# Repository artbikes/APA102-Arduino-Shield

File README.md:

# APA102-Arduino-Shield
An APA102 Arduino shield influenced by the Neopixel shield offered by Adafruit.
http://imgur.com/a/hvsxp

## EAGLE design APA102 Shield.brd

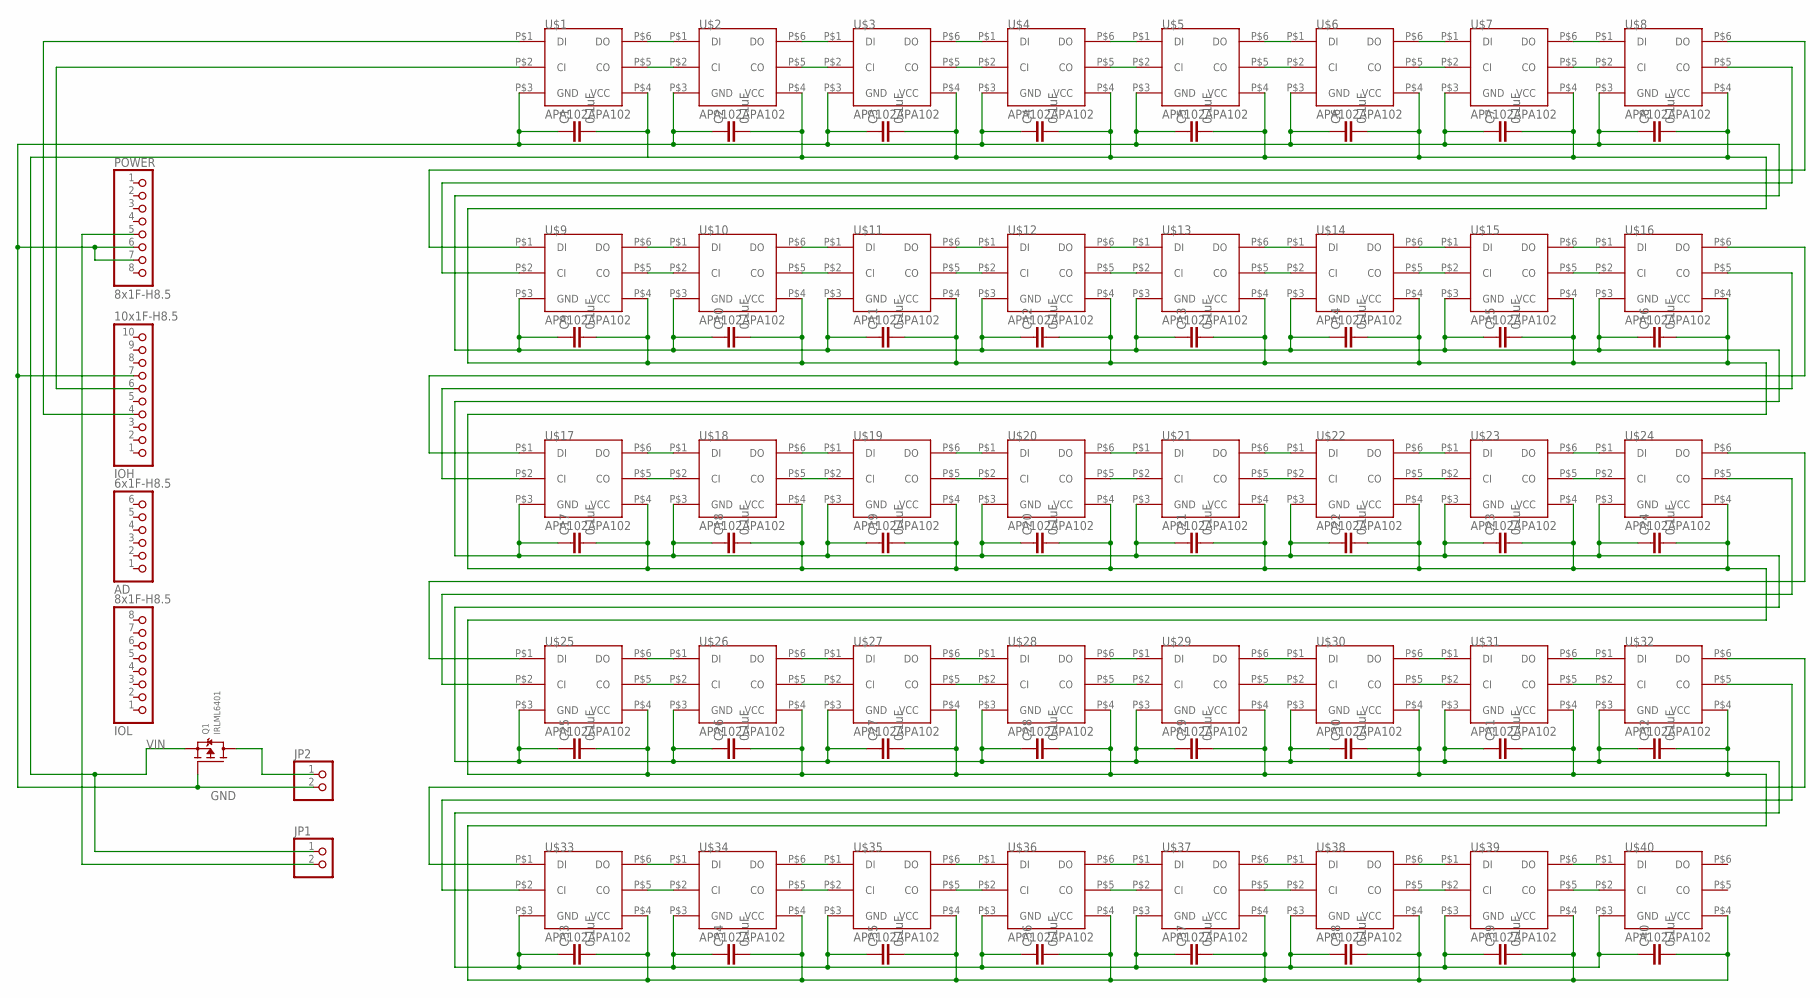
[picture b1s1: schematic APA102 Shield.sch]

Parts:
AD: 6x1F-H8.5; 1X06
C1, C2, C3, C4, C5, C6, C7, C8, C9, C10, C11, C12, C13, C14, C15, C16, C17, C18, C19, C20, C21, C22, C23, C24, C25, C26, C27, C28, C29, C30, C31, C32, C33, C34, C35, C36, C37, C38, C39, C40: 0.1uF; C1206
IOH: 10x1F-H8.5; 1X10
IOL: 8x1F-H8.5; 1X08
JP1, JP2: PINHD-1X2; 1X02
POWER: 8x1F-H8.5; 1X08
Q1: IRLML6401; SOT23-WIDE
U$1, U$2, U$3, U$4, U$5, U$6, U$7, U$8, U$9, U$10, U$11, U$12, U$13, U$14, U$15, U$16, U$17, U$18, U$19, U$20, U$21, U$22, U$23, U$24, U$25, U$26, U$27, U$28, U$29, U$30, U$31, U$32, U$33, U$34, U$35, U$36, U$37, U$38, U$39, U$40: APA102APA102; 5050

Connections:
GND: C1.1, C2.1, C3.1, C4.1, C5.1, C6.1, C7.1, C8.1, C9.1, C10.1, C11.1, C12.1, C13.1, C14.1, C15.1, C16.1, C17.1, C18.1, C19.1, C20.1, C21.1, C22.1, C23.1, C24.1, C25.1, C26.1, C27.1, C28.1, C29.1, C30.1, C31.1, C32.1, C33.1, C34.1, C35.1, C36.1, C37.1, C38.1, C39.1, C40.1, IOH.7, JP2.2, POWER.6, POWER.7, Q1.1 (G), U$1.P$3 (GND), U$2.P$3 (GND), U$3.P$3 (GND), U$4.P$3 (GND), U$5.P$3 (GND), U$6.P$3 (GND), U$7.P$3 (GND), U$8.P$3 (GND), U$9.P$3 (GND), U$10.P$3 (GND), U$11.P$3 (GND), U$12.P$3 (GND), U$13.P$3 (GND), U$14.P$3 (GND), U$15.P$3 (GND), U$16.P$3 (GND), U$17.P$3 (GND), U$18.P$3 (GND), U$19.P$3 (GND), U$20.P$3 (GND), U$21.P$3 (GND), U$22.P$3 (GND), U$23.P$3 (GND), U$24.P$3 (GND), U$25.P$3 (GND), U$26.P$3 (GND), U$27.P$3 (GND), U$28.P$3 (GND), U$29.P$3 (GND), U$30.P$3 (GND), U$31.P$3 (GND), U$32.P$3 (GND), U$33.P$3 (GND), U$34.P$3 (GND), U$35.P$3 (GND), U$36.P$3 (GND), U$37.P$3 (GND), U$38.P$3 (GND), U$39.P$3 (GND), U$40.P$3 (GND)
unnamed: IOH.4, U$1.P$1 (DI)
unnamed: U$15.P$5 (CO), U$16.P$2 (CI)
unnamed: U$23.P$6 (DO), U$24.P$1 (DI)
unnamed: U$15.P$6 (DO), U$16.P$1 (DI)
unnamed: IOH.6, U$1.P$2 (CI)
unnamed: U$14.P$6 (DO), U$15.P$1 (DI)
unnamed: U$14.P$5 (CO), U$15.P$2 (CI)
unnamed: U$7.P$6 (DO), U$8.P$1 (DI)
unnamed: U$7.P$5 (CO), U$8.P$2 (CI)
unnamed: U$6.P$6 (DO), U$7.P$1 (DI)
unnamed: U$6.P$5 (CO), U$7.P$2 (CI)
unnamed: U$5.P$6 (DO), U$6.P$1 (DI)
unnamed: U$5.P$5 (CO), U$6.P$2 (CI)
unnamed: U$4.P$6 (DO), U$5.P$1 (DI)
unnamed: U$4.P$5 (CO), U$5.P$2 (CI)
unnamed: U$3.P$6 (DO), U$4.P$1 (DI)
unnamed: U$3.P$5 (CO), U$4.P$2 (CI)
unnamed: U$2.P$6 (DO), U$3.P$1 (DI)
unnamed: U$2.P$5 (CO), U$3.P$2 (CI)
unnamed: U$1.P$6 (DO), U$2.P$1 (DI)
unnamed: U$1.P$5 (CO), U$2.P$2 (CI)
unnamed: U$23.P$5 (CO), U$24.P$2 (CI)
unnamed: U$13.P$6 (DO), U$14.P$1 (DI)
unnamed: U$22.P$6 (DO), U$23.P$1 (DI)
unnamed: U$13.P$5 (CO), U$14.P$2 (CI)
unnamed: U$12.P$6 (DO), U$13.P$1 (DI)
unnamed: U$12.P$5 (CO), U$13.P$2 (CI)
unnamed: U$11.P$6 (DO), U$12.P$1 (DI)
unnamed: U$11.P$5 (CO), U$12.P$2 (CI)
unnamed: U$10.P$6 (DO), U$11.P$1 (DI)
unnamed: U$10.P$5 (CO), U$11.P$2 (CI)
unnamed: U$9.P$6 (DO), U$10.P$1 (DI)
unnamed: U$9.P$5 (CO), U$10.P$2 (CI)
unnamed: U$22.P$5 (CO), U$23.P$2 (CI)
unnamed: U$16.P$5 (CO), U$17.P$2 (CI)
unnamed: U$8.P$5 (CO), U$9.P$2 (CI)
unnamed: U$8.P$6 (DO), U$9.P$1 (DI)
unnamed: U$16.P$6 (DO), U$17.P$1 (DI)
unnamed: U$39.P$6 (DO), U$40.P$1 (DI)
unnamed: U$21.P$6 (DO), U$22.P$1 (DI)
unnamed: U$21.P$5 (CO), U$22.P$2 (CI)
unnamed: U$20.P$6 (DO), U$21.P$1 (DI)
unnamed: U$20.P$5 (CO), U$21.P$2 (CI)
unnamed: U$19.P$6 (DO), U$20.P$1 (DI)
unnamed: U$19.P$5 (CO), U$20.P$2 (CI)
unnamed: U$18.P$6 (DO), U$19.P$1 (DI)
unnamed: U$18.P$5 (CO), U$19.P$2 (CI)
unnamed: U$17.P$6 (DO), U$18.P$1 (DI)
unnamed: U$17.P$5 (CO), U$18.P$2 (CI)
unnamed: U$39.P$5 (CO), U$40.P$2 (CI)
unnamed: U$38.P$6 (DO), U$39.P$1 (DI)
unnamed: U$31.P$6 (DO), U$32.P$1 (DI)
unnamed: U$31.P$5 (CO), U$32.P$2 (CI)
unnamed: U$30.P$6 (DO), U$31.P$1 (DI)
unnamed: U$30.P$5 (CO), U$31.P$2 (CI)
unnamed: U$29.P$6 (DO), U$30.P$1 (DI)
unnamed: U$29.P$5 (CO), U$30.P$2 (CI)
unnamed: U$28.P$6 (DO), U$29.P$1 (DI)
unnamed: U$28.P$5 (CO), U$29.P$2 (CI)
unnamed: U$27.P$6 (DO), U$28.P$1 (DI)
unnamed: U$27.P$5 (CO), U$28.P$2 (CI)
unnamed: U$26.P$6 (DO), U$27.P$1 (DI)
unnamed: U$26.P$5 (CO), U$27.P$2 (CI)
unnamed: U$25.P$6 (DO), U$26.P$1 (DI)
unnamed: U$25.P$5 (CO), U$26.P$2 (CI)
unnamed: U$38.P$5 (CO), U$39.P$2 (CI)
unnamed: U$24.P$5 (CO), U$25.P$2 (CI)
unnamed: U$24.P$6 (DO), U$25.P$1 (DI)
unnamed: JP1.2, POWER.5
unnamed: JP2.1, Q1.3 (D)
unnamed: U$37.P$6 (DO), U$38.P$1 (DI)
unnamed: U$37.P$5 (CO), U$38.P$2 (CI)
unnamed: U$36.P$6 (DO), U$37.P$1 (DI)
unnamed: U$36.P$5 (CO), U$37.P$2 (CI)
unnamed: U$35.P$6 (DO), U$36.P$1 (DI)
unnamed: U$35.P$5 (CO), U$36.P$2 (CI)
unnamed: U$34.P$6 (DO), U$35.P$1 (DI)
unnamed: U$34.P$5 (CO), U$35.P$2 (CI)
unnamed: U$33.P$6 (DO), U$34.P$1 (DI)
unnamed: U$33.P$5 (CO), U$34.P$2 (CI)
unnamed: U$32.P$5 (CO), U$33.P$2 (CI)
unnamed: U$32.P$6 (DO), U$33.P$1 (DI)
VIN: C1.2, C2.2, C3.2, C4.2, C5.2, C6.2, C7.2, C8.2, C9.2, C10.2, C11.2, C12.2, C13.2, C14.2, C15.2, C16.2, C17.2, C18.2, C19.2, C20.2, C21.2, C22.2, C23.2, C24.2, C25.2, C26.2, C27.2, C28.2, C29.2, C30.2, C31.2, C32.2, C33.2, C34.2, C35.2, C36.2, C37.2, C38.2, C39.2, C40.2, JP1.1, Q1.2 (S), U$1.P$4 (VCC), U$2.P$4 (VCC), U$3.P$4 (VCC), U$4.P$4 (VCC), U$5.P$4 (VCC), U$6.P$4 (VCC), U$7.P$4 (VCC), U$8.P$4 (VCC), U$9.P$4 (VCC), U$10.P$4 (VCC), U$11.P$4 (VCC), U$12.P$4 (VCC), U$13.P$4 (VCC), U$14.P$4 (VCC), U$15.P$4 (VCC), U$16.P$4 (VCC), U$17.P$4 (VCC), U$18.P$4 (VCC), U$19.P$4 (VCC), U$20.P$4 (VCC), U$21.P$4 (VCC), U$22.P$4 (VCC), U$23.P$4 (VCC), U$24.P$4 (VCC), U$25.P$4 (VCC), U$26.P$4 (VCC), U$27.P$4 (VCC), U$28.P$4 (VCC), U$29.P$4 (VCC), U$30.P$4 (VCC), U$31.P$4 (VCC), U$32.P$4 (VCC), U$33.P$4 (VCC), U$34.P$4 (VCC), U$35.P$4 (VCC), U$36.P$4 (VCC), U$37.P$4 (VCC), U$38.P$4 (VCC), U$39.P$4 (VCC), U$40.P$4 (VCC)

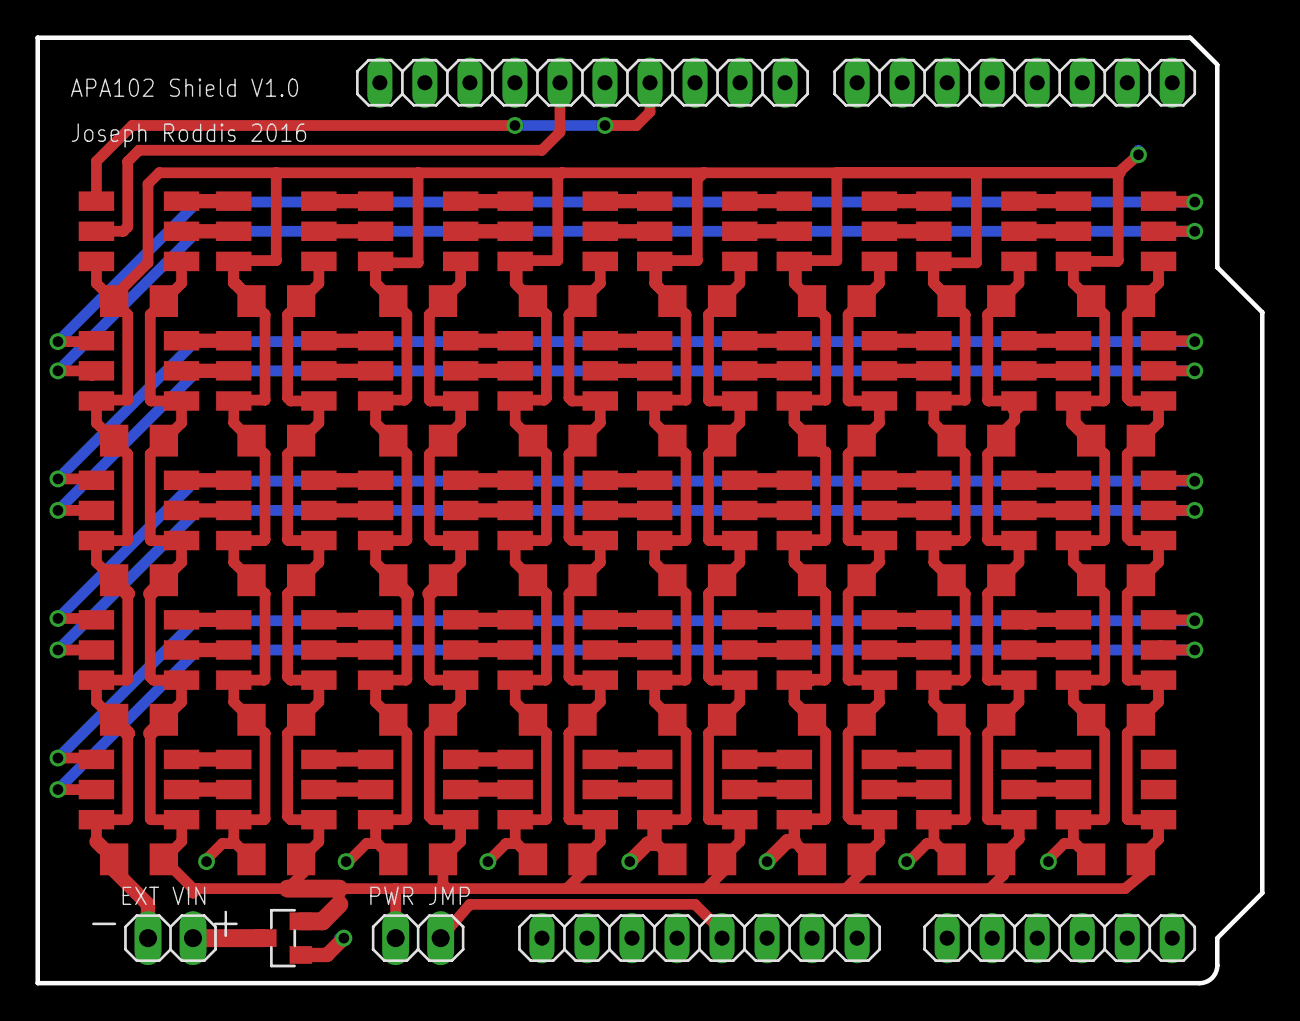
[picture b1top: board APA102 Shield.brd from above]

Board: 2 copper layers, 69.1 x 53.3 mm, 87 parts (0 on the bottom side), 84 nets.
